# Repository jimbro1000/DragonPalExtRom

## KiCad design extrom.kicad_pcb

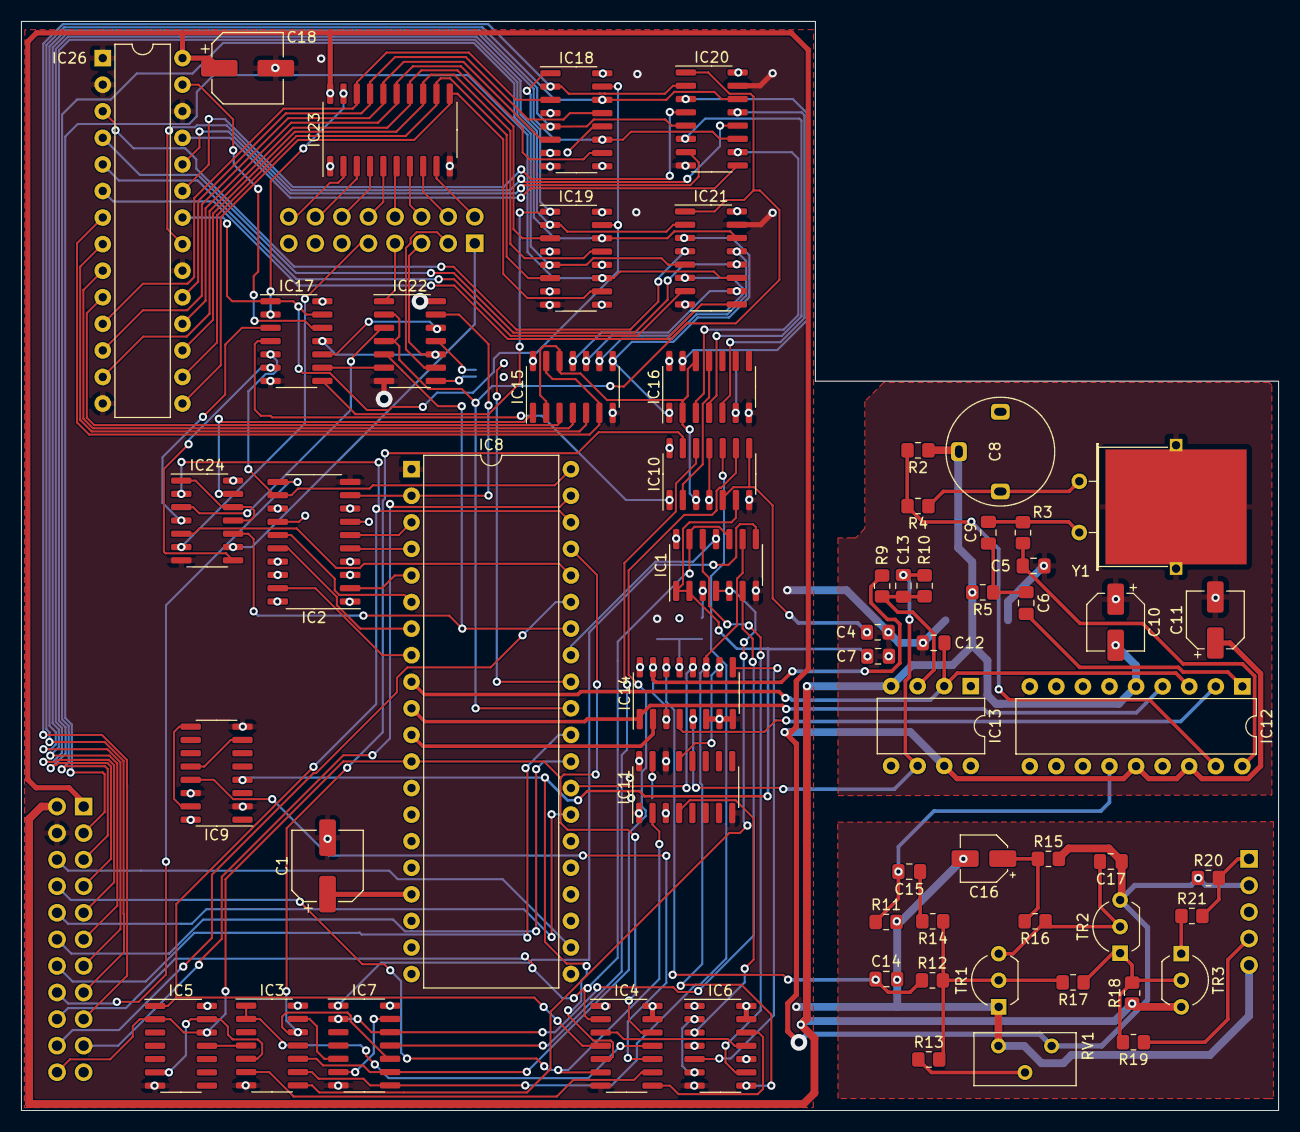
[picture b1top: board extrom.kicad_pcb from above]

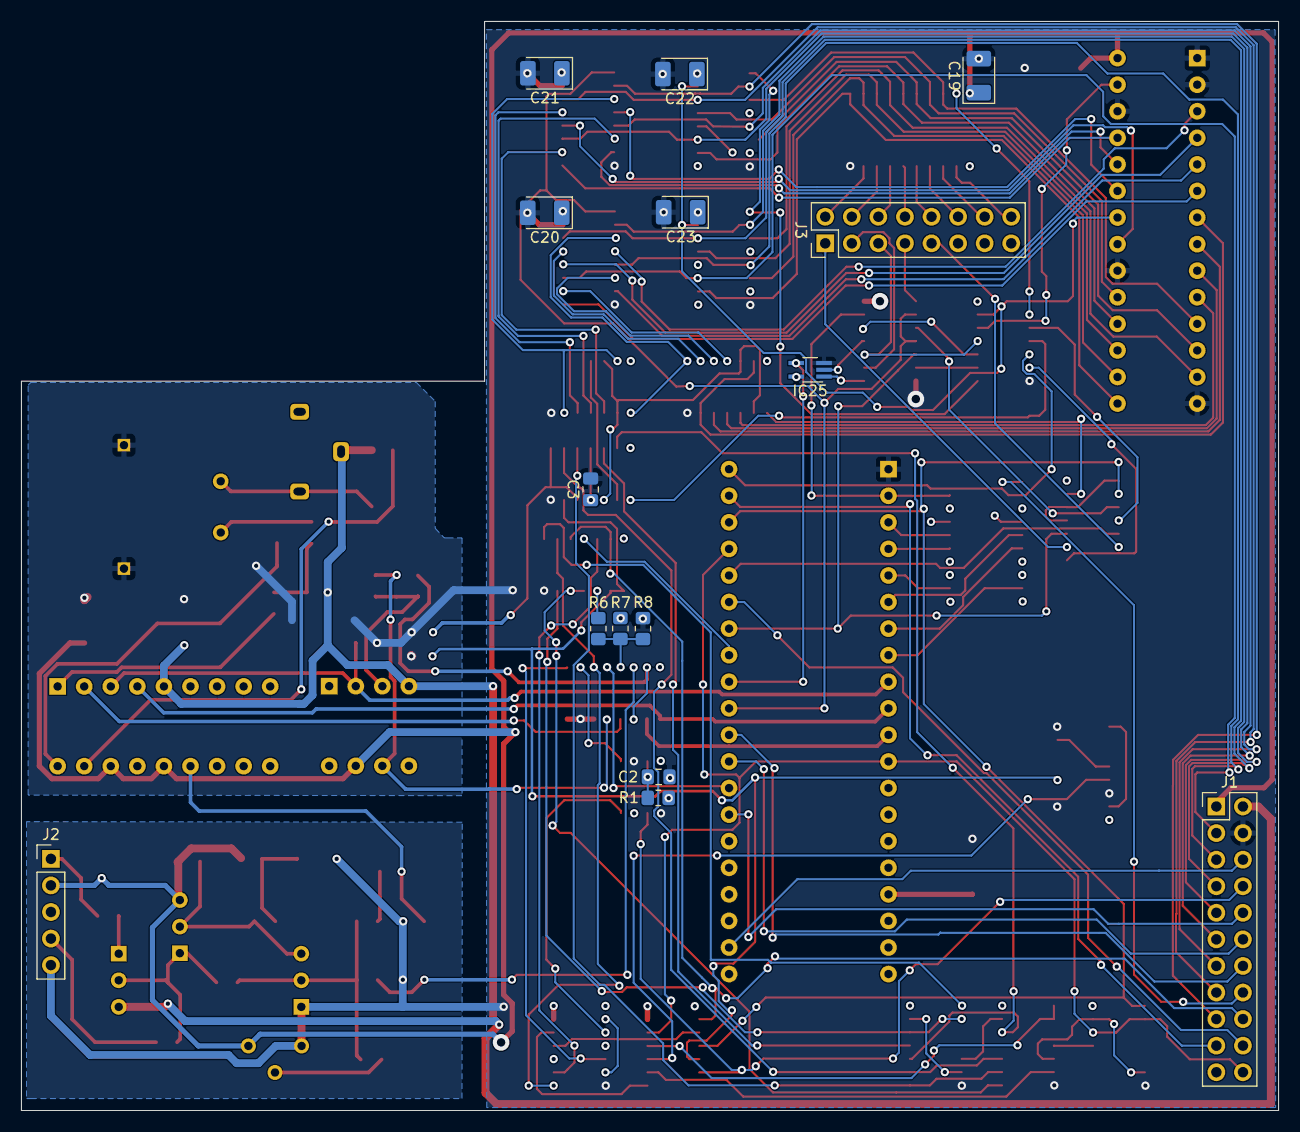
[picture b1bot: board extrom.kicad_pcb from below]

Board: 4 copper layers, 120.2 x 104.1 mm, 78 parts (15 on the bottom side), 155 nets.

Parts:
C1, C18: 100uF; CP_Elec_6.3x5.8
C2: 330pF; C_0805_2012Metric_Pad1.18x1.45mm_HandSolder
C3, C7: 180pF; C_0805_2012Metric_Pad1.18x1.45mm_HandSolder
C4: 100pF; C_0805_2012Metric_Pad1.18x1.45mm_HandSolder
C5, C9: 33pF; C_0805_2012Metric_Pad1.18x1.45mm_HandSolder
C6: 0.1uF; C_0805_2012Metric_Pad1.18x1.45mm_HandSolder
C8: 2-22pF; Trimmer-7.5mm
C10: 4.7uF; CP_Elec_5x5.8
C11: 47uF; CP_Elec_5x5.8
C12, C15: 0.01uF; C_0805_2012Metric_Pad1.18x1.45mm_HandSolder
C13: 4.7pF; C_0805_2012Metric_Pad1.18x1.45mm_HandSolder
C14, C17: 22pF; C_0805_2012Metric_Pad1.18x1.45mm_HandSolder
C16: 1uF; CP_Elec_4x5.4
C19, C20, C21, C22, C23: 100uF; CP_EIA-3528-21_Kemet-B_Pad1.50x2.35mm_HandSolder
IC1: 74HCT00; SOIC-14_3.9x8.7mm_P1.27mm
IC2: 74HC273; SO-20_5.3x12.6mm_P1.27mm
IC3: 74HCT20; SOIC-14_3.9x8.7mm_P1.27mm
IC4: 74HCT86; SOIC-14_3.9x8.7mm_P1.27mm
IC5, IC7, IC15, IC16: 74HCT393; SOIC-14_3.9x8.7mm_P1.27mm
IC6: 74ALS74N; SOIC-14_3.9x8.7mm_P1.27mm
IC8: MC6847; DIP-40_W15.24mm
IC9: 74HCT390; SOIC-16_3.9x9.9mm_P1.27mm
IC10: 74HCT32; SOIC-14_3.9x8.7mm_P1.27mm
IC11: 74LS123N; SOIC-16_3.9x9.9mm_P1.27mm
IC12: LM1889N; DIP-18_W7.62mm
IC13: 2318; DIP-8_W7.62mm
IC14: CD4053; SOIC-16_3.9x9.9mm_P1.27mm
IC17: 74HCT04; SOIC-14_3.9x8.7mm_P1.27mm
IC18, IC19, IC20, IC21: 74HCT257; SOIC-16_3.9x9.9mm_P1.27mm
IC22: 74HCT08; SOIC-14_3.9x8.7mm_P1.27mm
IC23: 74HCT245; SO-20_5.3x12.6mm_P1.27mm
IC24: 74HCT02; SOIC-14_3.9x8.7mm_P1.27mm
IC25: 74HCT1G32; SOT-353_SC-70-5_Handsoldering
IC26: HM62256BLP; DIP-28_W7.62mm
J1: Board Interconnect male; PinHeader_2x11_P2.54mm_Vertical
J2: Video Output male; PinHeader_1x05_P2.54mm_Vertical
J3: Conn_02x08_Odd_Even; PinHeader_2x08_P2.54mm_Vertical
R1: 27K; R_0805_2012Metric_Pad1.20x1.40mm_HandSolder
R2: 3K3; R_0805_2012Metric_Pad1.20x1.40mm_HandSolder
R3, R5, R12: 1K; R_0805_2012Metric_Pad1.20x1.40mm_HandSolder
R4, R16: 5K6; R_0805_2012Metric_Pad1.20x1.40mm_HandSolder
R6: 12K; R_0805_2012Metric_Pad1.20x1.40mm_HandSolder
R7: 8K2; R_0805_2012Metric_Pad1.20x1.40mm_HandSolder
R8: 1K8; R_0805_2012Metric_Pad1.20x1.40mm_HandSolder
R9, R10: 10K; R_0805_2012Metric_Pad1.20x1.40mm_HandSolder
R11: 22K; R_0805_2012Metric_Pad1.20x1.40mm_HandSolder
R13, R14, R17: 2K7; R_0805_2012Metric_Pad1.20x1.40mm_HandSolder
R15: 1K2; R_0805_2012Metric_Pad1.20x1.40mm_HandSolder
R18: 330R; R_0805_2012Metric_Pad1.20x1.40mm_HandSolder
R19: 10R; R_0805_2012Metric_Pad1.20x1.40mm_HandSolder
R20, R21: 270R; R_0805_2012Metric_Pad1.20x1.40mm_HandSolder
RV1: 10K; Potentiometer_Bourns_3386X_Horizontal
TR1, TR2: 2N2369; TO-92_Inline_Wide
TR3: BC212; TO-92_Inline_Wide
Y1: 4.433619MHz; Crystal_HC49-U_Horizontal_1EP_style2

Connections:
+5V: C1.1, C11.1, C17.1, C18.1, C19.1, C20.1, C21.1, C22.1, C23.1, IC1.14 (VCC), IC2.1 (~Mr), IC2.20 (VCC), IC3.14 (VCC), IC4.1, IC4.13, IC4.14 (VCC), IC5.14 (VCC), IC6.1 (~R), IC6.4 (~S), IC6.10 (~S), IC6.13 (~R), IC6.14 (VCC), IC7.14 (VCC), IC8.17 (VCC), IC9.16 (VCC), IC10.14 (VCC), IC11.3 (Clr), IC11.16 (VCC), IC12.14 (+V_RF), IC12.16 (+V_Chroma), IC13.7 (V+), IC14.16 (VDD), IC15.14 (VCC), IC16.14 (VCC), IC17.14 (VCC), IC18.16 (VCC), IC19.16 (VCC), IC20.16 (VCC), IC21.16 (VCC), IC22.14 (VCC), IC23.1 (A->B), IC23.20 (VCC), IC24.14 (VCC), IC25.5 (VCC), IC26.28 (VCC), J1.1, J2.2, R1.2, R7.2, R15.2, R20.2, RV1.1, TR2.3 (C)
-5V: C8.2, C10.2, IC12.5 (GND), IC13.4 (V-), J1.2, R2.1, R5.2, R18.1, TR3.3 (C)
/VDG/DV0: IC2.6 (Q2), IC8.3 (D0)
/VDG/DV1: IC2.5 (Q1), IC8.4 (D1)
/VDG/DV2: IC2.2 (Q0), IC8.5 (D2)
/VDG/DV3: IC2.15 (Q5), IC8.6 (D3)
/VDG/DV4: IC2.16 (Q6), IC8.7 (D4)
/VDG/DV5: IC2.19 (Q7), IC8.8 (D5)
/VDG/FS': IC3.6, IC4.9
/VDG/LINE PULSES: C7.2, IC1.1, IC1.2, IC4.5, IC9.4 (~CP1), IC10.6
/VDG/~VCLK: IC1.8, IC7.1 (CP)
/VDG/~VCLK/16: IC7.6 (Q3), IC7.13 (CP)
AA0: IC15.3 (Q0), IC26.10 (A0)
AA1: IC15.4 (Q1), IC26.9 (A1)
AA2: IC15.5 (Q2), IC26.8 (A2)
AA3: IC15.6 (Q3), IC15.13 (CP), IC26.7 (A3)
AB4: IC15.11 (Q0), IC21.10 (I1d)
AB5: IC15.10 (Q1), IC21.6 (I1b)
AB6: IC15.9 (Q2), IC21.13 (I1c)
AB7: IC15.8 (Q3), IC16.1 (CP), IC21.3 (I1a)
AB8: IC16.3 (Q0), IC20.10 (I1d)
AB9: IC16.4 (Q1), IC20.6 (I1b)
AB10: IC16.5 (Q2), IC20.13 (I1c)
AB11: IC16.6 (Q3), IC16.13 (CP), IC20.3 (I1a)
AC4: IC21.9 (Zd), IC26.6 (A4)
AC5: IC21.7 (Zb), IC26.5 (A5)
AC6: IC21.12 (Zc), IC26.4 (A6)
AC7: IC21.4 (Za), IC26.3 (A7)
AC8: IC20.9 (Zd), IC26.25 (A8)
AC9: IC20.7 (Zb), IC26.24 (A9)
AC10: IC20.12 (Zc), IC26.21 (A10)
AC11: IC20.4 (Za), IC26.23 (A11)
AD0: IC8.22 (DA0), J1.6
Alpha: IC24.9, J3.1
BIAS: J2.1, R20.1, R21.2
CHB: C12.1, IC8.9 (CHB), IC12.3 (ChromaBias), IC13.2 (-)
CHROME CONTROL: IC6.5 (Q), IC14.9 (C)
CLK: IC1.11, IC8.33 (CLK)
CSS: IC8.39 (CSS), J1.19
ChrOSC: IC12.17 (ChromaOSC), R2.2, R4.2
Composite: C15.2, IC12.13 (ChromaSub), R11.1
D0: IC19.11 (I0d), IC21.11 (I0d), J1.3
D1: IC19.5 (I0b), IC21.5 (I0b), J1.5
D2: IC19.14 (I0c), IC21.14 (I0c), J1.7
D3: IC19.2 (I0a), IC21.2 (I0a), J1.9
D4: IC18.11 (I0d), IC20.11 (I0d), J1.11
D5: IC18.5 (I0b), IC20.5 (I0b), J1.13
D6: IC18.14 (I0c), IC20.14 (I0c), J1.15
D7: IC18.2 (I0a), IC20.2 (I0a), J1.17
DA0: IC19.10 (I1d), IC23.11 (B7), IC26.15 (Q3)
DA1: IC19.6 (I1b), IC23.12 (B6), IC26.16 (Q4)
DA2: IC19.13 (I1c), IC23.13 (B5), IC26.17 (Q5)
DA3: IC19.3 (I1a), IC23.14 (B4), IC26.13 (Q2)
DA4: IC18.10 (I1d), IC23.15 (B3), IC26.18 (Q6)
DA5: IC18.6 (I1b), IC23.16 (B2), IC26.12 (Q1)
DA6: IC18.13 (I1c), IC23.17 (B1), IC26.19 (Q7)
DA7: IC18.3 (I1a), IC23.18 (B0), IC26.11 (Q0)
DB0: IC2.7 (D2), IC19.9 (Zd)
DB1: IC2.4 (D1), IC19.7 (Zb)
DB2: IC2.3 (D0), IC19.12 (Zc)
DB3: IC2.14 (D5), IC19.4 (Za)
DB4: IC2.17 (D6), IC18.9 (Zd)
DB5: IC2.18 (D7), IC18.7 (Zb)
DB6: IC2.8 (D3), IC18.12 (Zc)
DB7: IC2.13 (D4), IC18.4 (Za)
DC0: IC23.9 (A7), J3.2
DC1: IC23.8 (A6), J3.4
DC2: IC23.7 (A5), J3.6
DC3: IC23.6 (A4), J3.8
DC4: IC23.5 (A3), J3.10
DC5: IC23.4 (A2), J3.12
DC6: IC23.3 (A1), J3.14
DC7: IC23.2 (A0), J3.16
GM0: IC8.30 (GM0), J1.14
GM1: IC8.29 (GM1), J1.12
GM2: IC8.27 (GM2), J1.10
GND: C1.2, C2.2, C3.2, C4.2, C5.2, C7.1, C10.1, C11.2, C12.2, C14.2, C16.2, C18.2, C19.2, C20.2, C21.2, C22.2, C23.2, IC1.7 (GND), IC2.10 (GND), IC3.7 (GND), IC4.7 (GND), IC5.7 (GND), IC6.7 (GND), IC7.7 (GND), IC8.1 (GND), IC9.2 (MR), IC9.8 (GND), IC9.14 (MR), IC10.7 (GND), IC11.1 (A), IC11.8 (GND), IC11.14 (Cext), IC14.6 (INHIBIT), IC14.7 (VEE), IC14.8 (VSS), IC15.7 (GND), IC16.7 (GND), IC17.7 (GND), IC18.8 (GND), IC19.8 (GND), IC20.8 (GND), IC20.15 (OE), IC21.8 (GND), IC21.15 (OE), IC22.7 (GND), IC23.10 (GND), IC24.7 (GND), IC25.3 (GND), IC26.1 (A14), IC26.2 (A12), IC26.14 (GND), IC26.20 (~CS), IC26.26 (A13), J1.4, J2.5, R8.1, R11.2, RV1.3, TR1.1 (E), Y1.3
INV: IC2.9 (Q3), IC8.2 (D6), IC22.13
INV': IC8.32 (INV), IC25.4
Inverse: IC22.9, J3.3
LAG: C5.1, IC12.18 (ChromaLag), R3.2
LEAD: C6.2, IC12.1 (ChromaLead)
LINE PULSE: IC14.13 (X1), R6.1, R7.1, R8.2
LUM: IC8.28 (Y), IC14.12 (X0)
LUM CONTROL: IC1.9, IC6.8 (~Q), IC14.11 (A)
MAX_ADD: IC10.2, IC16.11 (Q0)
MR: IC10.3, IC15.2 (MR), IC15.12 (MR), IC16.2 (MR), IC16.12 (MR)
MUX X: C14.1, IC14.14 (X), R12.1
MUX Y: IC14.3 (Z1), IC14.15 (Y), R9.1
MUX Z: IC12.2 (R-Y), IC14.4 (Z)
unnamed: C3.1, IC10.4, IC10.11
unnamed: C4.1, IC10.5, IC10.8
unnamed: C6.1, C9.1, R5.1
unnamed: C8.1, R4.1, Y1.2
unnamed: C9.2, R3.1, Y1.1
unnamed: C15.1, R14.2
unnamed: C16.1, R15.1, R16.2
unnamed: IC1.3, R6.2
unnamed: IC1.4, IC1.5, IC3.8
unnamed: IC3.1, IC3.2, IC4.11
unnamed: IC3.5, IC5.6 (Q3), IC5.13 (CP)
unnamed: IC3.4, IC5.11 (Q0)
unnamed: IC6.2 (D), IC6.6 (~Q)
unnamed: IC4.3, IC6.11 (C)
unnamed: IC4.8, IC6.12 (D)
unnamed: IC1.12, IC6.9 (Q)
unnamed: IC1.6, IC7.2 (MR), IC7.12 (MR)
unnamed: IC3.13, IC7.5 (Q2)
unnamed: IC7.11 (Q0), IC10.12
unnamed: IC3.12, IC7.10 (Q1), IC10.13
unnamed: IC3.10, IC7.9 (Q2), IC10.9
unnamed: IC3.9, IC7.8 (Q3), IC10.10
unnamed: IC9.7 (Q3), IC9.12 (~CP1)
unnamed: IC4.10, IC9.13 (Q0)
unnamed: IC9.9 (Q3), IC9.15 (~CP0)
unnamed: IC10.1, IC17.4
unnamed: C2.1, IC11.15 (RCext), R1.1
unnamed: IC6.3 (C), IC11.4 (~Q)
unnamed: C13.1, IC13.3 (+), R9.2, R10.1
unnamed: C13.2, IC13.6, IC14.5 (Z0), R10.2
unnamed: IC15.1 (CP), IC24.13
unnamed: IC17.3, IC24.4
unnamed: IC17.6, IC24.8
unnamed: IC17.9, IC22.6
unnamed: IC17.10, IC22.12
unnamed: IC22.3, IC24.3
unnamed: IC22.8, IC25.1
unnamed: IC22.11, IC25.2
unnamed: IC17.2, IC23.19 (CE)
unnamed: IC24.1, IC24.11, IC24.12
unnamed: IC17.12, IC26.27 (~WE)
unnamed: R13.1, RV1.2
unnamed: R12.2, R13.2, R14.1, R17.2, TR1.2 (B)
unnamed: C17.2, R16.1, TR1.3 (C), TR2.2 (B)
unnamed: R17.1, R18.2, R19.2, TR2.1 (E), TR3.2 (B)
unnamed: R21.1, TR3.1 (E)
RC: IC24.6, J3.9
RClk: IC22.1, J3.7
SELA: IC17.8, IC18.1 (S), IC19.1 (S)
SYNC CONTROL: IC11.13 (Q), IC14.10 (B)
VCLK: IC1.10, IC1.13, IC4.2, J1.18
VID OUT: J2.4, R19.1
phiA: IC8.11 (A), IC14.2 (Y0)
phiB: IC8.10 (B), IC12.4 (B-Y), IC14.1 (Y1)
~A/G: IC8.35 (~A/G), J1.20
~A/S: IC2.12 (Q4), IC8.40 (D7), IC17.5
~A/S': IC8.34 (~A/S), IC22.5, IC24.10
~FS: IC4.12, IC5.2 (MR), IC5.12 (MR), IC8.12 (~MS), IC8.37 (~FS), J1.22
~HS: IC4.4, IC5.1 (CP), IC8.38 (~HS), IC24.2
~INT/EXT: IC8.31 (~INT/EXT), IC20.1 (S), IC21.1 (S), IC22.2, IC22.4
~NHS: IC4.6, IC11.2 (B), J1.8
~RAS0: IC2.11 (Cp), J1.16
~RP: IC8.36 (~RP), IC24.5
~R/W: IC17.1, IC17.13, IC18.15 (OE), IC19.15 (OE), IC26.22 (~OE)
~SelInv: IC17.11, IC22.10, J3.5

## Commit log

2023-09-01 rework pcb
2023-10-01 wired board
